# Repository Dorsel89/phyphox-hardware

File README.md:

# phyphox Hardware

This repository will contain manufacturing files of phyphox hardware projects

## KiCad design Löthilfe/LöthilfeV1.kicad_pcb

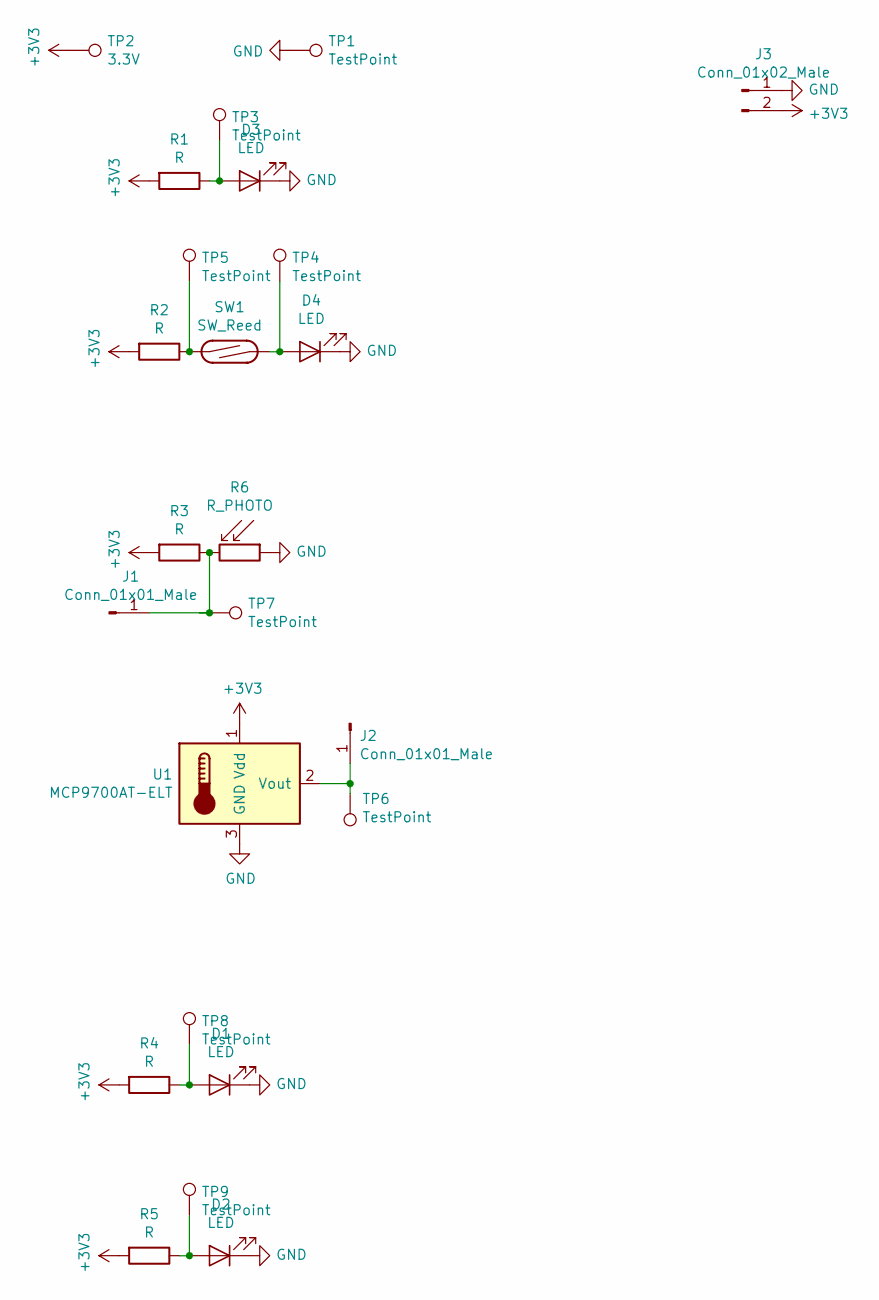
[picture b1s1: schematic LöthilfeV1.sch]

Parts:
D1: LED; LED_1206_3216Metric_Pad1.42x1.75mm_HandSolder
D2: LED; LED_0805_2012Metric_Pad1.15x1.40mm_HandSolder
D3, D4: LED; LED_D5.0mm
J1, J2: Conn_01x01_Male; PinHeader_1x01_P2.54mm_Vertical
J3: Conn_01x02_Male; PinHeader_1x02_P2.54mm_Vertical
R1, R2, R3: R; R_Axial_DIN0207_L6.3mm_D2.5mm_P15.24mm_Horizontal
R4: R; R_1206_3216Metric_Pad1.42x1.75mm_HandSolder
R5: R; R_0805_2012Metric_Pad1.15x1.40mm_HandSolder
R6: R_PHOTO; R_LDR_5.2x5.2mm_P3.5mm_Horizontal
SW1: SW_Reed; R_Axial_DIN0516_L15.5mm_D5.0mm_P25.40mm_Horizontal
TP1, TP3, TP4, TP5, TP6, TP7, TP8, TP9: TestPoint; TestPoint_Loop_D3.50mm_Drill1.4mm_Beaded
TP2: 3.3V; TestPoint_Loop_D3.50mm_Drill1.4mm_Beaded
U1: MCP9700AT-ELT; TO-92L_Inline

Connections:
+3V3: J3.2, R1.2, R2.2, R3.2, R4.2, R5.2, TP2.1, U1.1 (Vdd)
GND: D1.1 (K), D2.1 (K), D3.1 (K), D4.1 (K), J3.1, R6.1, TP1.1, U1.3 (GND)
unnamed: D1.2 (A), R4.1, TP8.1
unnamed: D2.2 (A), R5.1, TP9.1
unnamed: D3.2 (A), R1.1, TP3.1
unnamed: D4.2 (A), SW1.2, TP4.1
unnamed: J1.1, R3.1, R6.2, TP7.1
unnamed: J2.1, TP6.1, U1.2 (Vout)
unnamed: R2.1, SW1.1, TP5.1

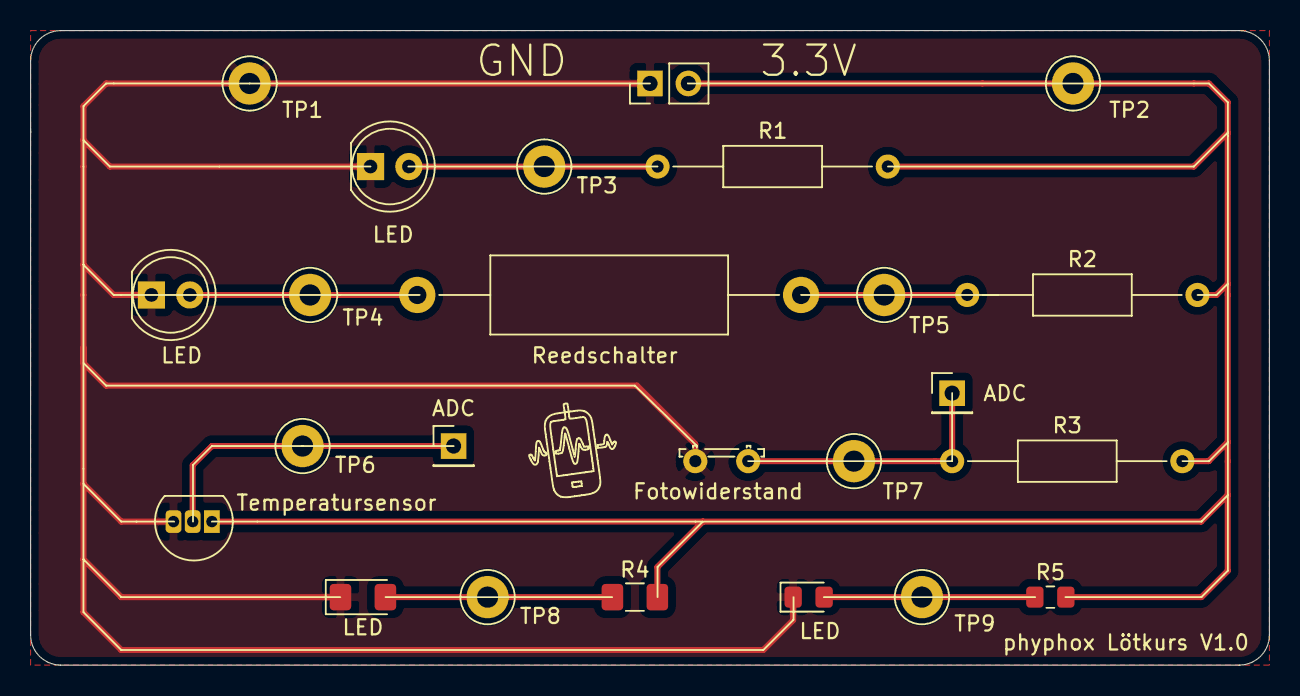
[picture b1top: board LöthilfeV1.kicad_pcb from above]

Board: 2 copper layers, 82.0 x 42.0 mm, 24 parts (0 on the bottom side), 9 nets.

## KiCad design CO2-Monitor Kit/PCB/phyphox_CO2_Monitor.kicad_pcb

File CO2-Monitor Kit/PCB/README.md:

# PCB of the phyphox CO₂-Monitor

Used components:
- RGB-LED: WP154A4SEJ3VBDZGW/CA
- BLE Mikrocontroller: ESP32-DEVKITC-32D
- Sensor: SCD30

Used software:
 - Kicad

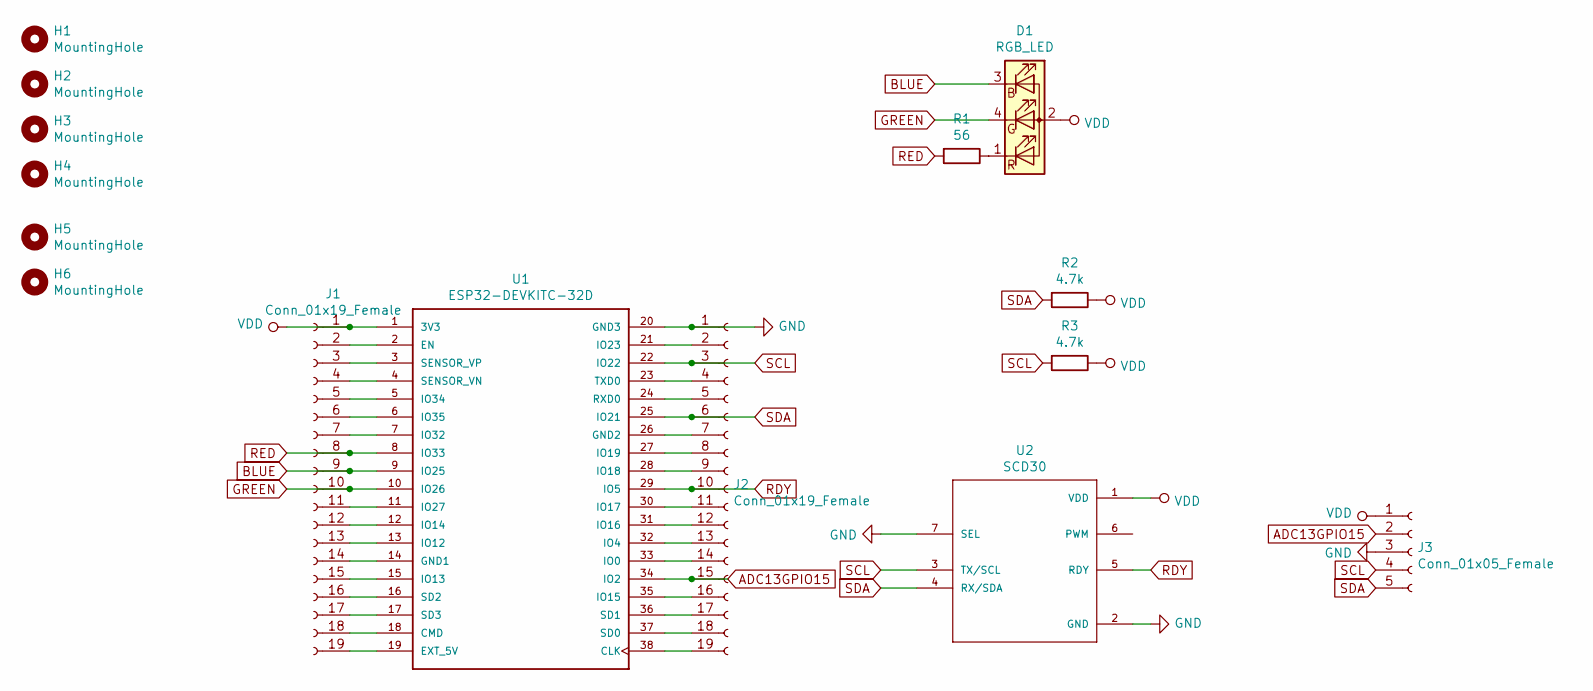
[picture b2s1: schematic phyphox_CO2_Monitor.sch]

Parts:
D1: RGB_LED; WP154A4SEJ3VBDZGWCA
H1, H2, H3, H4: MountingHole; MountingHoleM3
H5, H6: MountingHole; MountingHole_2mm
J1, J2: Conn_01x19_Female; PinSocket_1x19_P2.54mm_Vertical
J3: Conn_01x05_Female; PinHeader_1x05_P2.54mm_Vertical
R1: 56; R_Axial_DIN0309_L9.0mm_D3.2mm_P15.24mm_Horizontal
R2, R3: 4.7k; R_Axial_DIN0309_L9.0mm_D3.2mm_P15.24mm_Horizontal
U1: ESP32-DEVKITC-32D; ESP32-DevKitC-32D
U2: SCD30

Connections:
ADC13GPIO15: J2.15, J3.2, U1.34 (IO2)
BLUE: D1.3 (RK), J1.9, U1.9 (IO25)
GND: J2.1, J3.3, U1.20 (GND3), U2.2 (GND), U2.7 (SEL)
GREEN: D1.4 (GK), J1.10, U1.10 (IO26)
unnamed: D1.1 (BK), R1.1
unnamed: J1.2, U1.2 (EN)
unnamed: J1.3, U1.3 (SENSOR_VP)
unnamed: J1.4, U1.4 (SENSOR_VN)
unnamed: J1.5, U1.5 (IO34)
unnamed: J1.6, U1.6 (IO35)
unnamed: J1.7, U1.7 (IO32)
unnamed: J1.11, U1.11 (IO27)
unnamed: J1.12, U1.12 (IO14)
unnamed: J1.13, U1.13 (IO12)
unnamed: J1.14, U1.14 (GND1)
unnamed: J1.15, U1.15 (IO13)
unnamed: J1.16, U1.16 (SD2)
unnamed: J1.17, U1.17 (SD3)
unnamed: J1.18, U1.18 (CMD)
unnamed: J1.19, U1.19 (EXT_5V)
unnamed: J2.2, U1.21 (IO23)
unnamed: J2.4, U1.23 (TXD0)
unnamed: J2.5, U1.24 (RXD0)
unnamed: J2.7, U1.26 (GND2)
unnamed: J2.8, U1.27 (IO19)
unnamed: J2.9, U1.28 (IO18)
unnamed: J2.11, U1.30 (IO17)
unnamed: J2.12, U1.31 (IO16)
unnamed: J2.13, U1.32 (IO4)
unnamed: J2.14, U1.33 (IO0)
unnamed: J2.16, U1.35 (IO15)
unnamed: J2.17, U1.36 (SD1)
unnamed: J2.18, U1.37 (SD0)
unnamed: J2.19, U1.38 (CLK)
RDY: J2.10, U1.29 (IO5), U2.5 (RDY)
RED: J1.8, R1.2, U1.8 (IO33)
SCL: J2.3, J3.4, R3.2, U1.22 (IO22), U2.3 (TX/SCL)
SDA: J2.6, J3.5, R2.2, U1.25 (IO21), U2.4 (RX/SDA)
VDD: D1.2 (A), J1.1, J3.1, R2.1, R3.1, U1.1 (3V3), U2.1 (VDD)

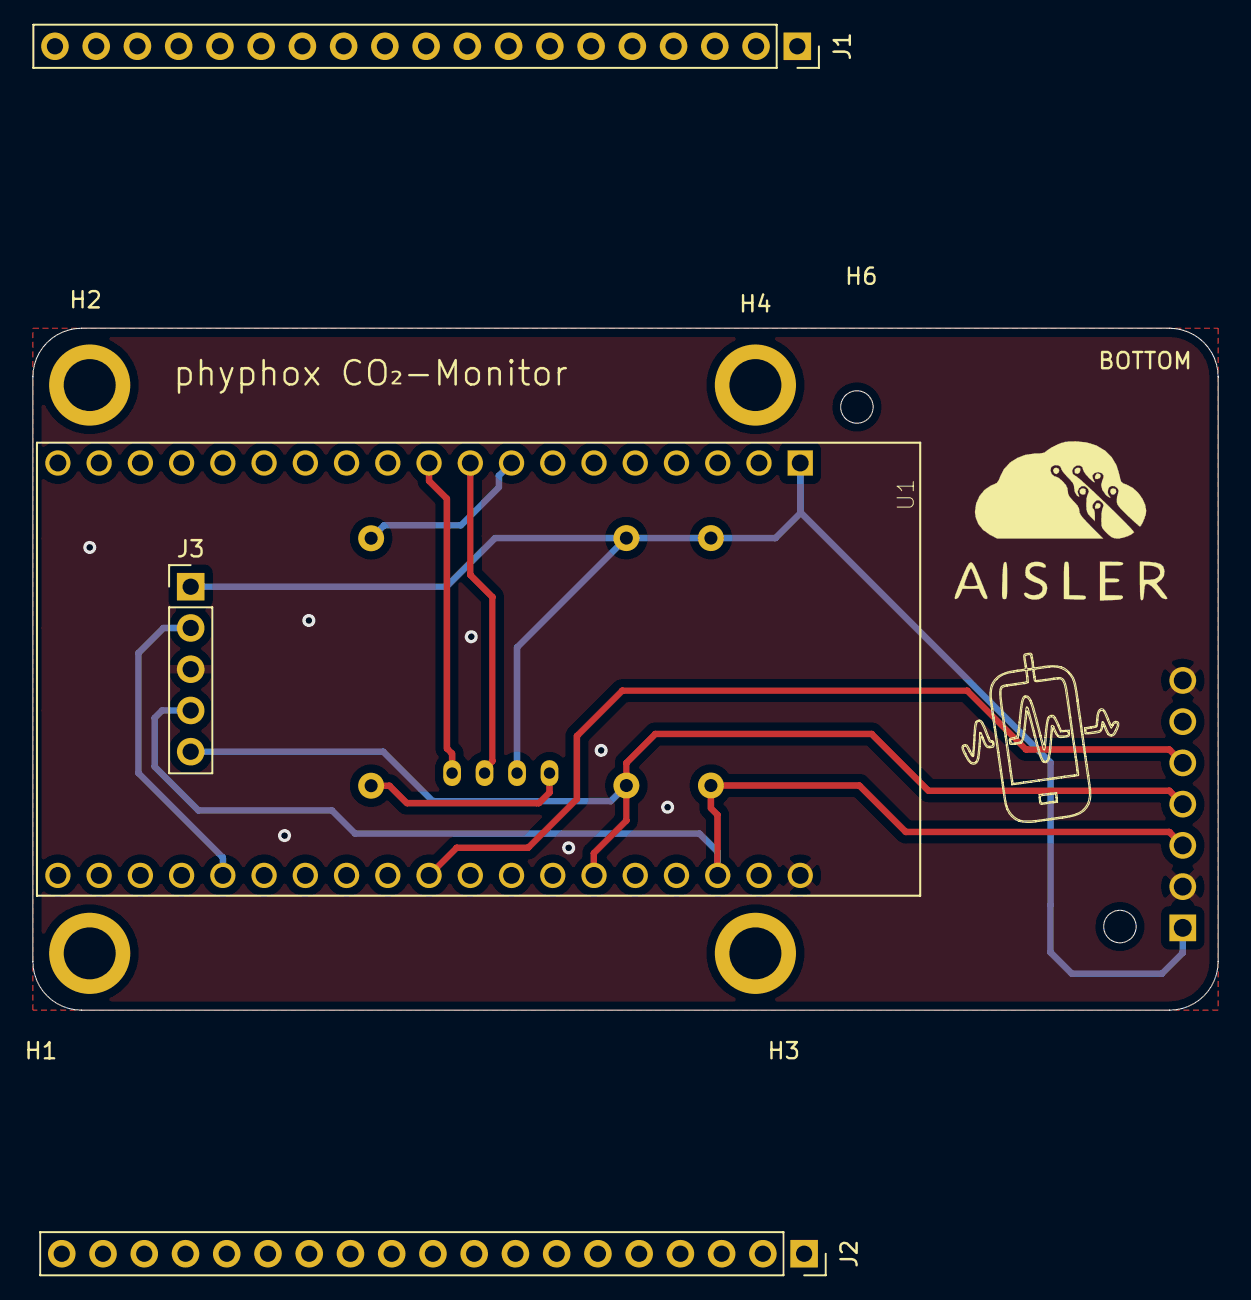
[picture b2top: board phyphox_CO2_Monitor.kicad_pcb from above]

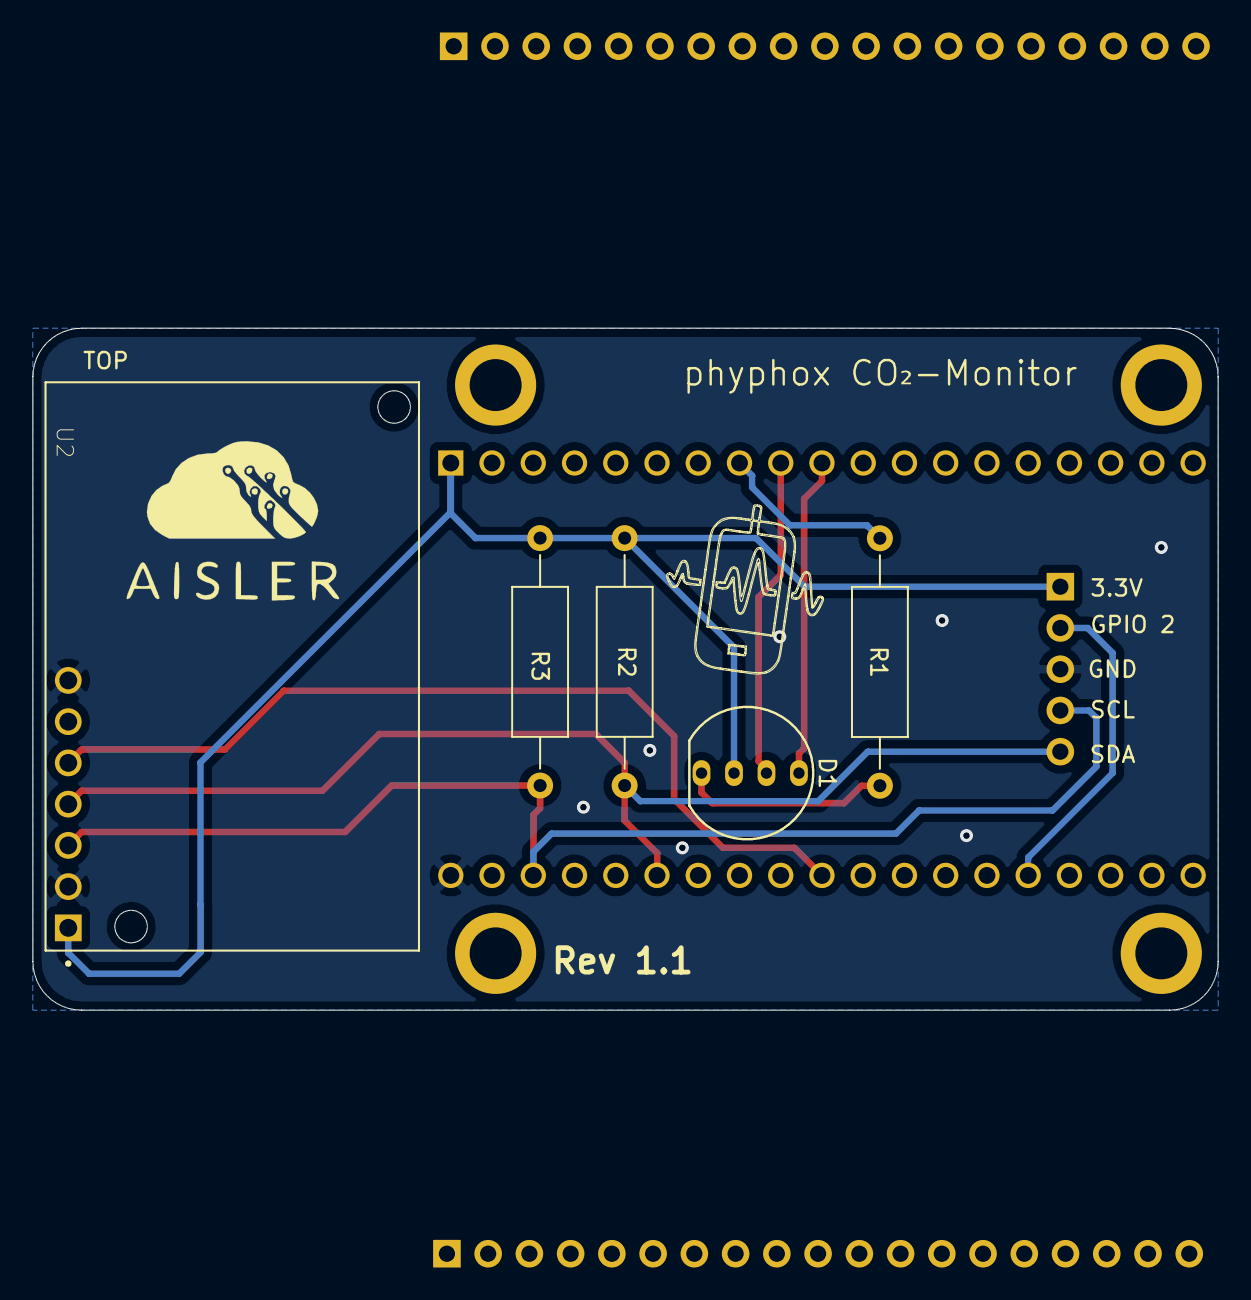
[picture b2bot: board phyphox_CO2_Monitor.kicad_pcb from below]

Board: 2 copper layers, 73.0 x 42.0 mm, 15 parts (5 on the bottom side), 39 nets.

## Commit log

2020-09-28 init
2020-09-30 horizontal design
2020-09-30 revision 0.6
2020-10-21 gerber files generated
2020-10-21 Create LICENSE
2020-11-06 [REV 1] Mounting Holes M2.5 -> M3, I2C port available
2020-11-06 [Rev 1] STL updatet, Lasercut design added
2020-11-13 [CO2 Monitor] update lasercut housing
2020-12-07 [CO2Kit] Update manufacturing files
2020-12-13 [CO2Kit] phyphox experiments added
2021-02-05 [CO2-Kit] Update PCB to Rev 1.1
2021-02-05 [CO2-Kit] revised temperature compensation
2021-03-15 Silkscreen updated
2021-08-25 Lasercut-Gehäuse optimiert
2022-03-03 Update Maintenance Experiment
2023-02-06 Update lasercut description
2023-07-05 Added Lötkurs
